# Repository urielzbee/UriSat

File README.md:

# UriSat
Cube satelite "UriSat" is intended to be launched on a weather ballon.

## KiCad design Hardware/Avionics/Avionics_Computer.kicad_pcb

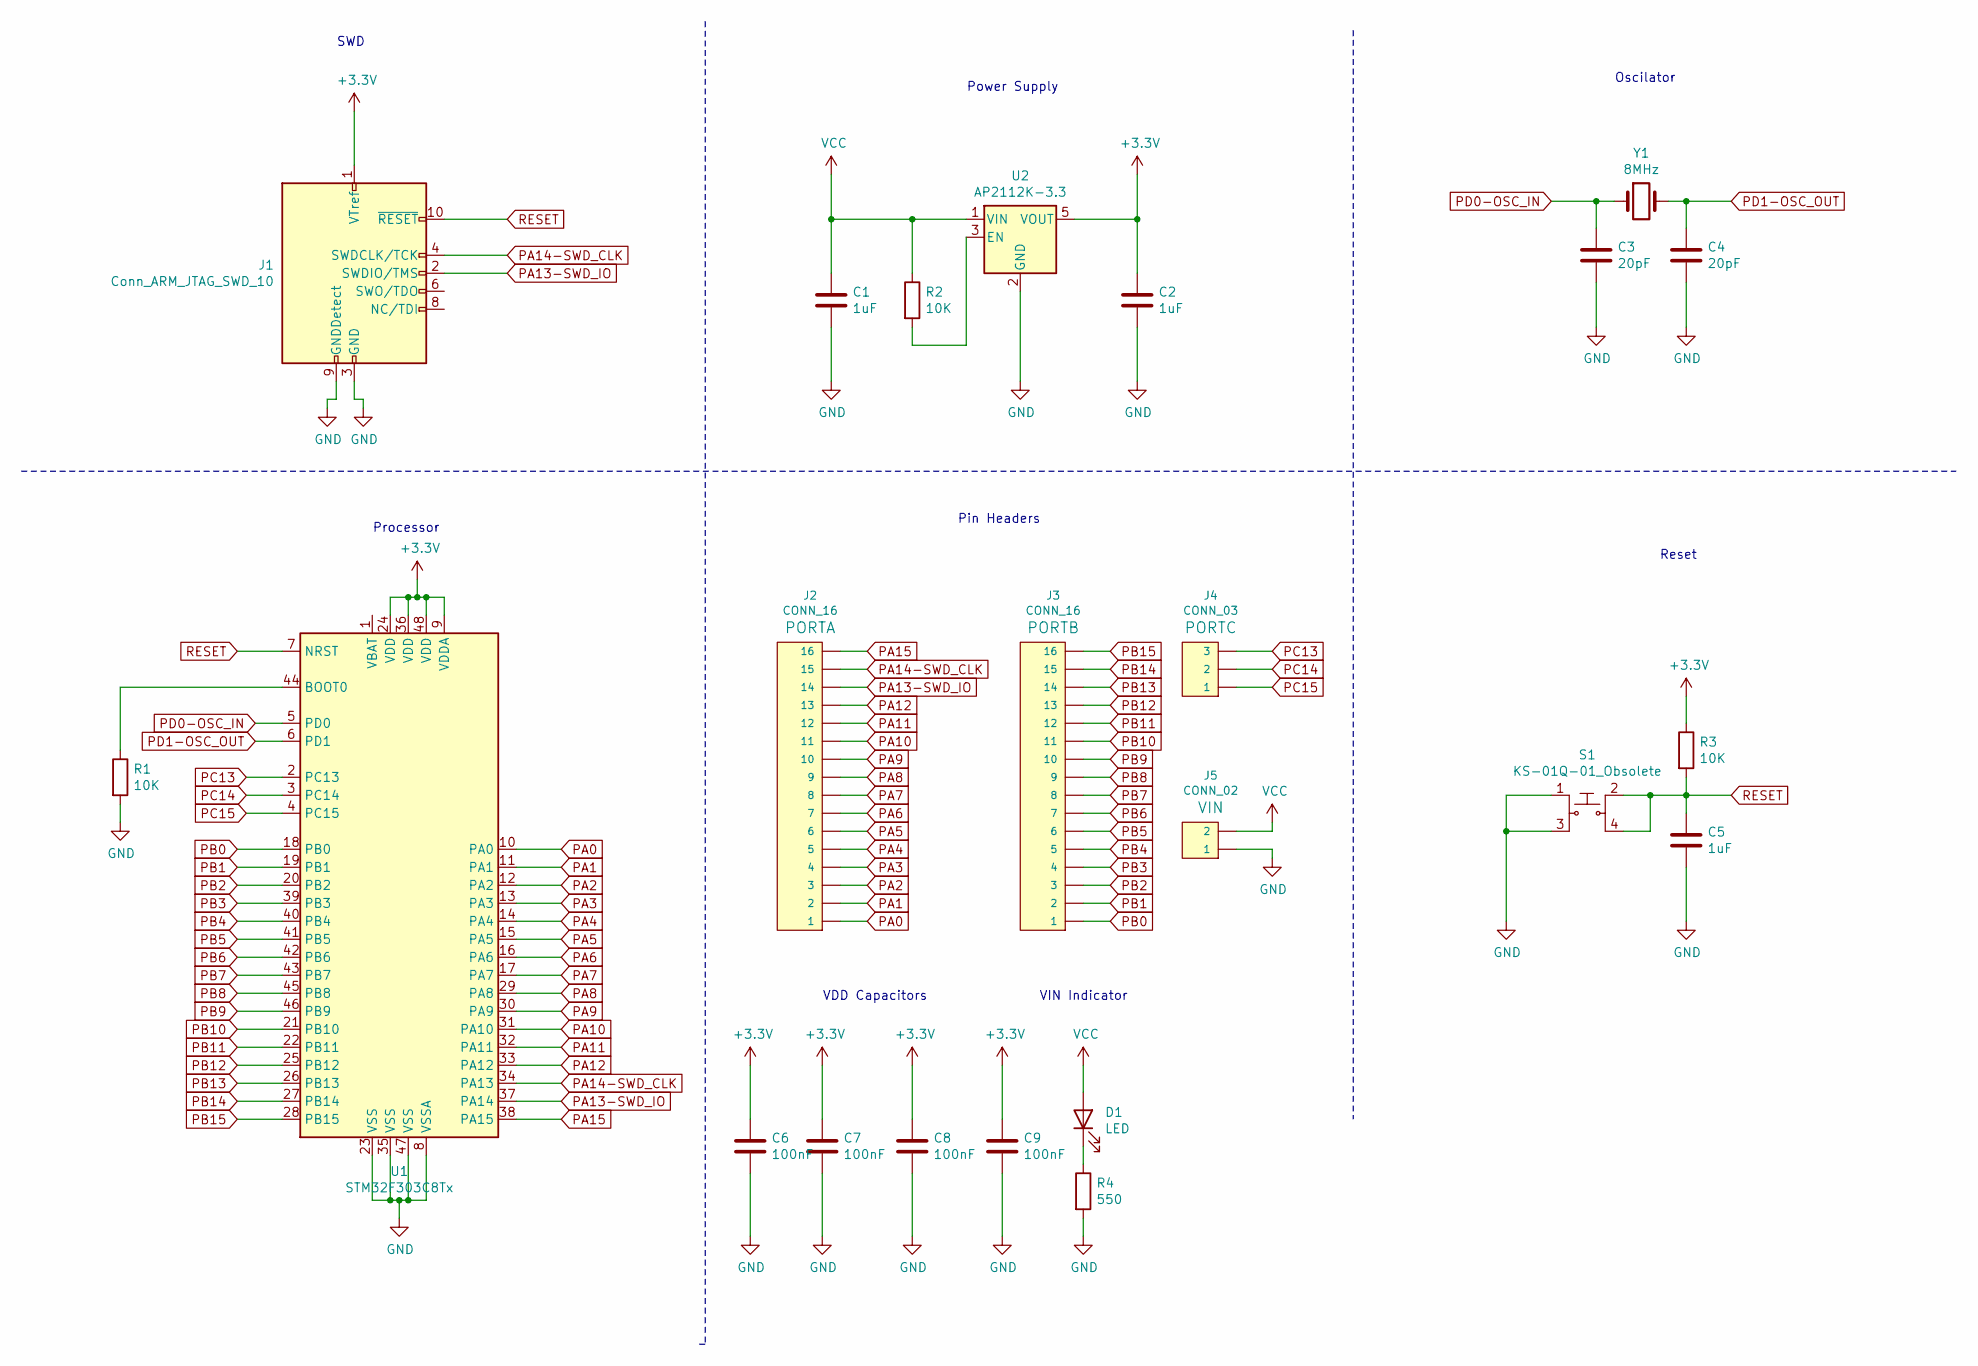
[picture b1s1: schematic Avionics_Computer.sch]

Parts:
C1, C2, C5: 1uF; C_0805_2012Metric
C3, C4: 20pF; C_0805_2012Metric
C6, C7, C8, C9: 100nF; C_0805_2012Metric
D1: LED; LED_0805_2012Metric
J1: Conn_ARM_JTAG_SWD_10; PinHeader_2x05_P1.27mm_Vertical
J2, J3: CONN_16; 1X16
J4: CONN_03; 1X03
J5: CONN_02; 1X02
R1, R2, R3: 10K; R_0805_2012Metric
R4: 550; R_0805_2012Metric
S1: KS-01Q-01_Obsolete; SW_SPST_Omron_B3FS-100xP; MPN KS-01Q-01; Digi-Key_PN EG4791-ND
U1: STM32F303C8Tx; LQFP-48_7x7mm_P0.5mm
U2: AP2112K-3.3; SOT-23-5
Y1: 8MHz; Crystal_HC18-U_Vertical

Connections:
+3V3: C2.1, C6.1, C7.1, C8.1, C9.1, J1.1 (VTref), R3.1, U1.9 (VDDA), U1.24 (VDD), U1.36 (VDD), U1.48 (VDD), U2.5 (VOUT)
GND: C1.2, C2.2, C3.2, C4.2, C5.2, C6.2, C7.2, C8.2, C9.2, J1.3 (GND), J1.5 (GND), J1.9 (GNDDetect), J5.1, R1.2, R4.2, S1.1, S1.3, U1.8 (VSSA), U1.23 (VSS), U1.35 (VSS), U1.47 (VSS), U2.2 (GND)
unnamed: D1.1 (K), R4.1
unnamed: R1.1, U1.44 (BOOT0)
unnamed: R2.2, U2.3 (EN)
PA0: J2.1, U1.10 (PA0)
PA1: J2.2, U1.11 (PA1)
PA2: J2.3, U1.12 (PA2)
PA3: J2.4, U1.13 (PA3)
PA4: J2.5, U1.14 (PA4)
PA5: J2.6, U1.15 (PA5)
PA6: J2.7, U1.16 (PA6)
PA7: J2.8, U1.17 (PA7)
PA8: J2.9, U1.29 (PA8)
PA9: J2.10, U1.30 (PA9)
PA10: J2.11, U1.31 (PA10)
PA11: J2.12, U1.32 (PA11)
PA12: J2.13, U1.33 (PA12)
PA13-SWD_IO: J1.2 (SWDIO/TMS), J2.14, U1.37 (PA14)
PA14-SWD_CLK: J1.4 (SWDCLK/TCK), J2.15, U1.34 (PA13)
PA15: J2.16, U1.38 (PA15)
PB0: J3.1, U1.18 (PB0)
PB1: J3.2, U1.19 (PB1)
PB2: J3.3, U1.20 (PB2)
PB3: J3.4, U1.39 (PB3)
PB4: J3.5, U1.40 (PB4)
PB5: J3.6, U1.41 (PB5)
PB6: J3.7, U1.42 (PB6)
PB7: J3.8, U1.43 (PB7)
PB8: J3.9, U1.45 (PB8)
PB9: J3.10, U1.46 (PB9)
PB10: J3.11, U1.21 (PB10)
PB11: J3.12, U1.22 (PB11)
PB12: J3.13, U1.25 (PB12)
PB13: J3.14, U1.26 (PB13)
PB14: J3.15, U1.27 (PB14)
PB15: J3.16, U1.28 (PB15)
PC13: J4.3, U1.2 (PC13)
PC14: J4.2, U1.3 (PC14)
PC15: J4.1, U1.4 (PC15)
PD0-OSC_IN: C3.1, U1.5 (PD0), Y1.1
PD1-OSC_OUT: C4.1, U1.6 (PD1), Y1.2
RESET: C5.1, J1.10 (~RESET~), R3.2, S1.2, S1.4, U1.7 (NRST)
VCC: C1.1, D1.2 (A), J5.2, R2.1, U2.1 (VIN)

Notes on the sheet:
SWD
Power Supply
Oscilator
Reset
Pin Headers
Processor
VIN Indicator
VDD Capacitors

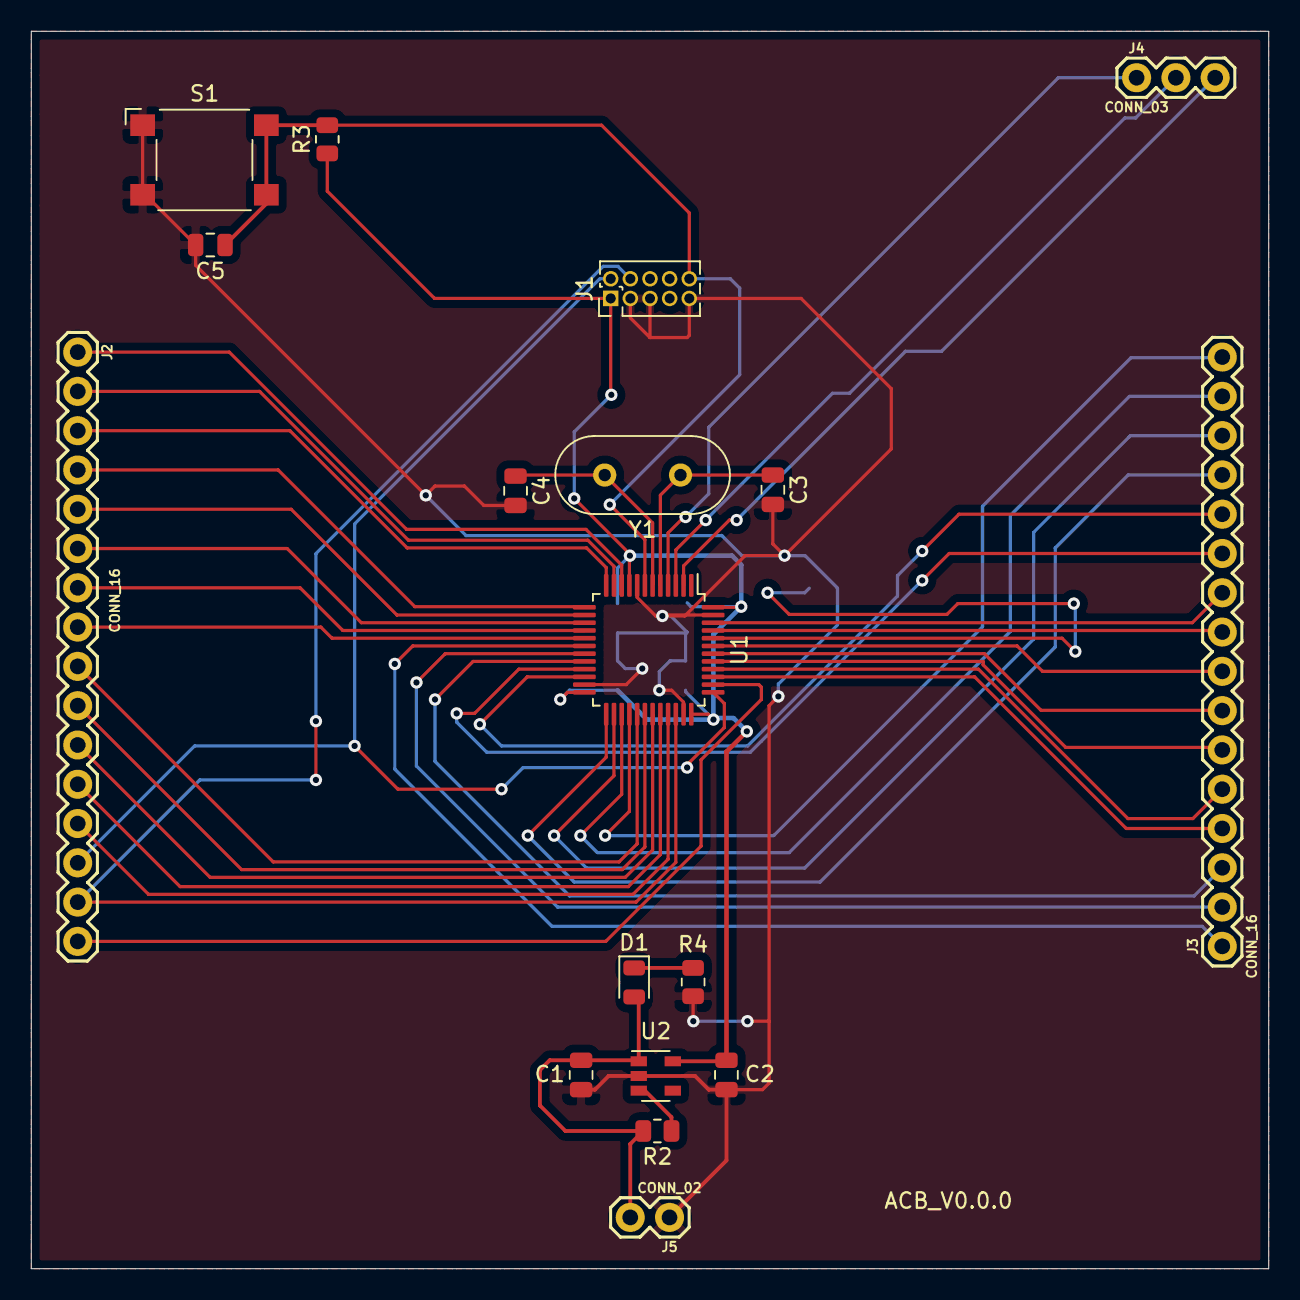
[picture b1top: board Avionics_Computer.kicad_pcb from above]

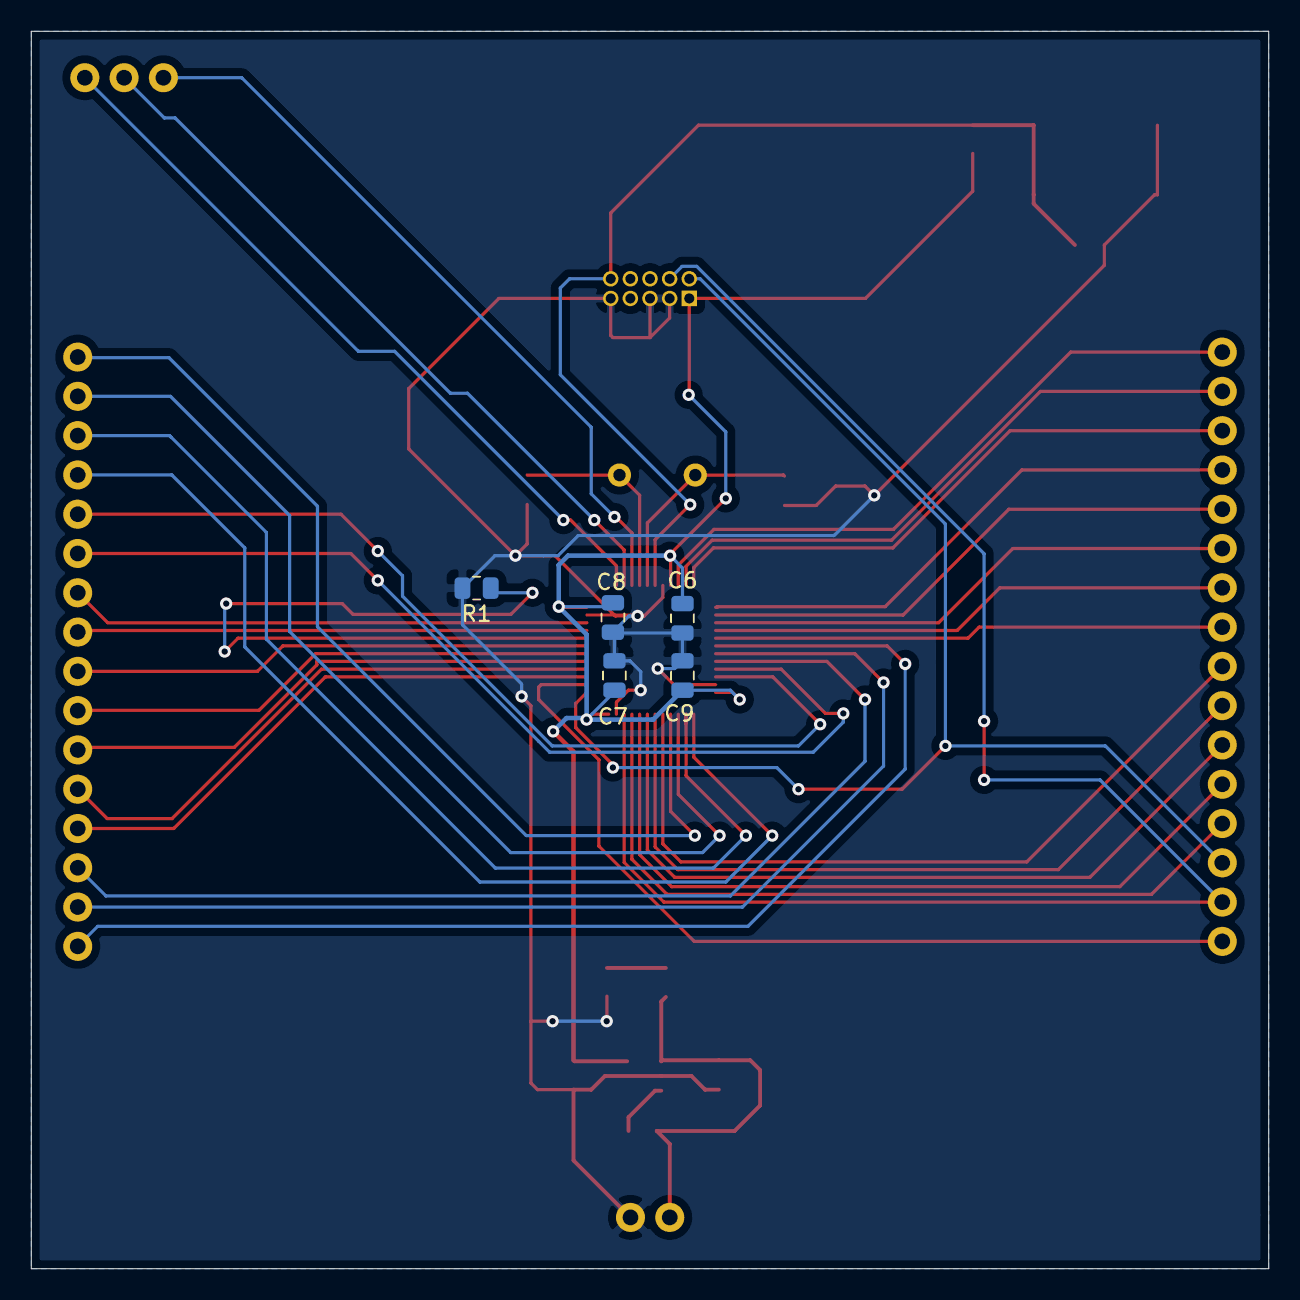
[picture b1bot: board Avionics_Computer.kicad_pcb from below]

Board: 2 copper layers, 80.0 x 80.0 mm, 23 parts (5 on the bottom side), 44 nets.

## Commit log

2021-03-30 First commit since release. Selection of MCU, Temp Sensor.
2021-03-31 Added SPI Flash, Voltage LEDs, User LED, Reset Button, BOOT 0 Button, USB Mini Connector, Pin Headers
2021-04-01 Finished schematic connections, assigning of component name and value, selection of footprints, sheet specification
2021-04-03 Added PCB desgin, modification on the schematic for a better pcb layout, generation of Gerber files and BOM. In this commit the PCB design files where sent to manufacture and the components where ord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
2021-04-06 Update README.md file
    Added a simple description
2021-05-28 Create LICENSE
